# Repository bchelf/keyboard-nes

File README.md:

# keyboard-nes

Remapping order: Right, Left, Down, Up, A, B, Select, Start

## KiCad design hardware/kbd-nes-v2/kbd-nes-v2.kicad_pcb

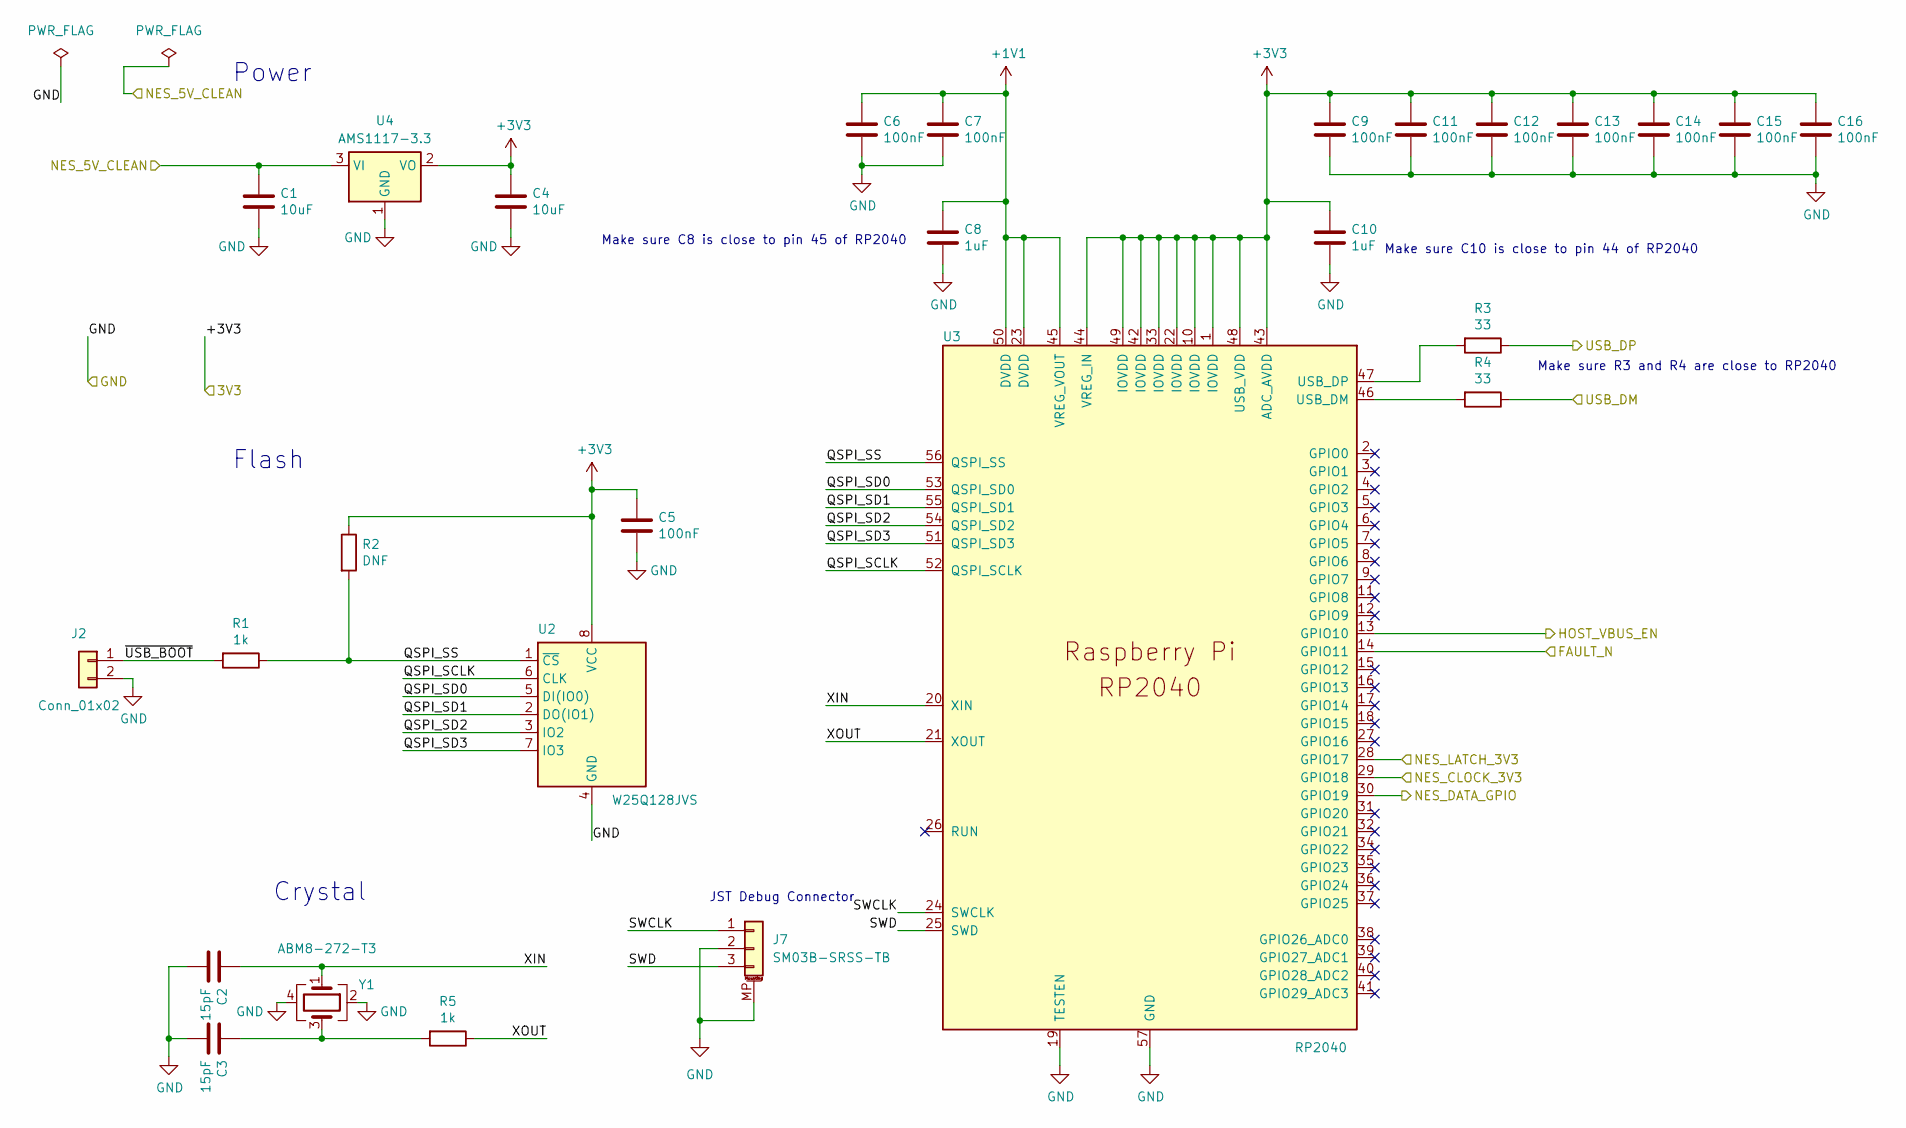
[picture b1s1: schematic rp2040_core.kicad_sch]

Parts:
C1, C4: 10uF; C_0603_1608Metric; LCSC C19702
C2, C3: 15pF; C_0402_1005Metric; LCSC C1548
C5, C6, C7, C9, C11, C12, C13, C14, C15, C16: 100nF; C_0402_1005Metric; LCSC C307331
C8, C10: 1uF; C_0402_1005Metric; LCSC C52923
J2: Conn_01x02; PinHeader_1x02_P2.54mm_Vertical
J7: SM03B-SRSS-TB; JST_SH_SM03B-SRSS-TB_1x03-1MP_P1.00mm_Horizontal; LCSC C160403
R1, R5: 1k; R_0402_1005Metric; LCSC C11702
R2: DNF; R_0402_1005Metric
R3, R4: 33; R_0402_1005Metric; LCSC C25105
U2: W25Q128JVS; SOIC-8_5.3x5.3mm_P1.27mm; LCSC C97521
U3: RP2040; QFN-56-1EP_7x7mm_P0.4mm_EP3.2x3.2mm_ThermalVias; LCSC C2040
U4: AMS1117-3.3; SOT-223-3_TabPin2; LCSC C6186
Y1: ABM8-272-T3; Crystal_SMD_3225-4Pin_3.2x2.5mm; LCSC C20625731

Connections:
+1V1: C6.1, C7.1, C8.1, U3.23 (DVDD), U3.45 (VREG_VOUT), U3.50 (DVDD)
+3V3: C4.1, C5.1, C9.1, C10.1, C11.1, C12.1, C13.1, C14.1, C15.1, C16.1, R2.1, U2.8 (VCC), U3.1 (IOVDD), U3.10 (IOVDD), U3.22 (IOVDD), U3.33 (IOVDD), U3.42 (IOVDD), U3.43 (ADC_AVDD), U3.44 (VREG_IN), U3.48 (USB_VDD), U3.49 (IOVDD), U4.2 (VO); also elsewhere on the board
/NES Input Output/NES_5V_CLEAN: C1.1, U4.3 (VI); also elsewhere on the board
/NES Input Output/NES_CLOCK_3V3: U3.29 (GPIO18); also elsewhere on the board
/NES Input Output/NES_DATA_GPIO: U3.30 (GPIO19); also elsewhere on the board
/NES Input Output/NES_LATCH_3V3: U3.28 (GPIO17); also elsewhere on the board
/RP2040 Core/FAULT_N: U3.14 (GPIO11); also elsewhere on the board
/RP2040 Core/HOST_VBUS_EN: U3.13 (GPIO10); also elsewhere on the board
/RP2040 Core/QSPI_SCLK: U2.6 (CLK), U3.52 (QSPI_SCLK)
/RP2040 Core/QSPI_SD0: U2.5 (DI(IO0)), U3.53 (QSPI_SD0)
/RP2040 Core/QSPI_SD1: U2.2 (DO(IO1)), U3.55 (QSPI_SD1)
/RP2040 Core/QSPI_SD2: U2.3 (IO2), U3.54 (QSPI_SD2)
/RP2040 Core/QSPI_SD3: U2.7 (IO3), U3.51 (QSPI_SD3)
/RP2040 Core/QSPI_SS: R1.1, R2.2, U2.1 (~CS), U3.56 (QSPI_SS)
/RP2040 Core/SWCLK: J7.1, U3.24 (SWCLK)
/RP2040 Core/SWD: J7.3, U3.25 (SWD)
/RP2040 Core/USB_DM: R4.1; also elsewhere on the board
/RP2040 Core/USB_DP: R3.1; also elsewhere on the board
/RP2040 Core/XIN: C2.1, U3.20 (XIN), Y1.1
/RP2040 Core/XOUT: R5.1, U3.21 (XOUT)
/RP2040 Core/~USB_BOOT: J2.1, R1.2
GND: C1.2, C2.2, C3.2, C4.2, C5.2, C6.2, C7.2, C8.2, C9.2, C10.2, C11.2, C12.2, C13.2, C14.2, C15.2, C16.2, J2.2, J7.2, J7.MP (MountPin), U2.4 (GND), U3.19 (TESTEN), U3.57 (GND), U4.1 (GND), Y1.2, Y1.4; also elsewhere on the board
unnamed: C3.1, R5.2, Y1.3
unnamed: R4.2, U3.46 (USB_DM)
unnamed: R3.2, U3.47 (USB_DP)

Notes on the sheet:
Make sure R3 and R4 are close to RP2040
JST Debug Connector
Crystal
Flash
Make sure C8 is close to pin 45 of RP2040
Make sure C10 is close to pin 44 of RP2040
Power

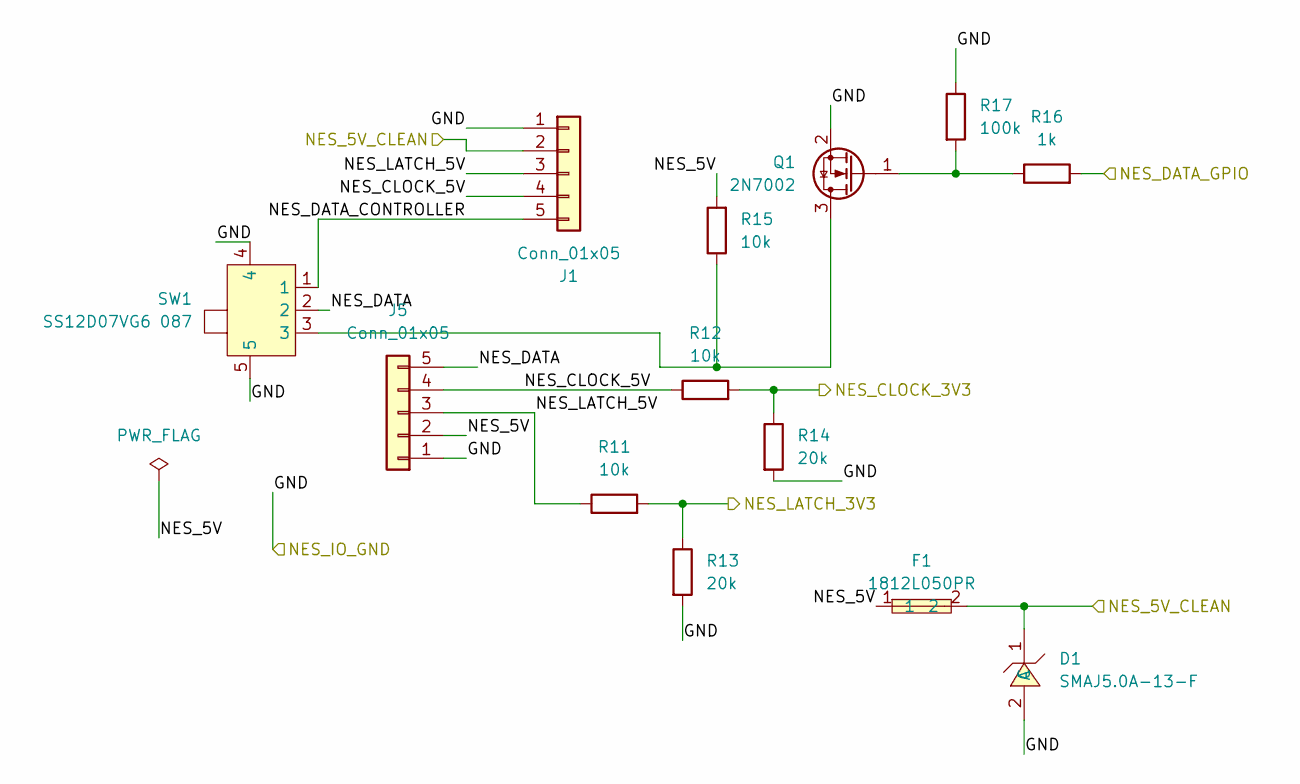
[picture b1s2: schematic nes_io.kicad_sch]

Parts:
D1: SMAJ5.0A-13-F; SMA_L4.3-W2.6-LS5.2-RD; MPN SMAJ5.0A-13-F; LCSC C87074
F1: 1812L050PR; F1812; MPN 1812L050PR; LCSC C151169
J1, J5: Conn_01x05; JST_PH_S5B-PH-SM4-TB_1x05-1MP_P2.00mm_Horizontal; LCSC C265104
Q1: 2N7002; SOT-23; LCSC C8545
R11, R12, R15: 10k; R_0402_1005Metric; LCSC C25744
R13, R14: 20k; R_0402_1005Metric; LCSC C25765
R16: 1k; R_0402_1005Metric; LCSC C11702
R17: 100k; R_0402_1005Metric; LCSC C25741
SW1: SS12D07VG6 087; SW-TH_SS12D07VG4; MPN SS12D07VG6 087; LCSC C2939728

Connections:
/NES Input Output/NES_5V: F1.1, J5.2, R15.2
/NES Input Output/NES_5V_CLEAN: D1.1 (C), F1.2, J1.2; also elsewhere on the board
/NES Input Output/NES_CLOCK_3V3: R12.2, R14.1; also elsewhere on the board
/NES Input Output/NES_CLOCK_5V: J1.4, J5.4, R12.1
/NES Input Output/NES_DATA: J5.5, SW1.2
/NES Input Output/NES_DATA_CONTROLLER: J1.5, SW1.1
/NES Input Output/NES_DATA_GPIO: R16.2; also elsewhere on the board
/NES Input Output/NES_LATCH_3V3: R11.2, R13.1; also elsewhere on the board
/NES Input Output/NES_LATCH_5V: J1.3, J5.3, R11.1
GND: D1.2 (A), J1.1, J5.1, Q1.2 (S), R13.2, R14.2, R17.1, SW1.4, SW1.5; also elsewhere on the board
unnamed: Q1.3 (D), R15.1, SW1.3
unnamed: Q1.1 (G), R16.1, R17.2

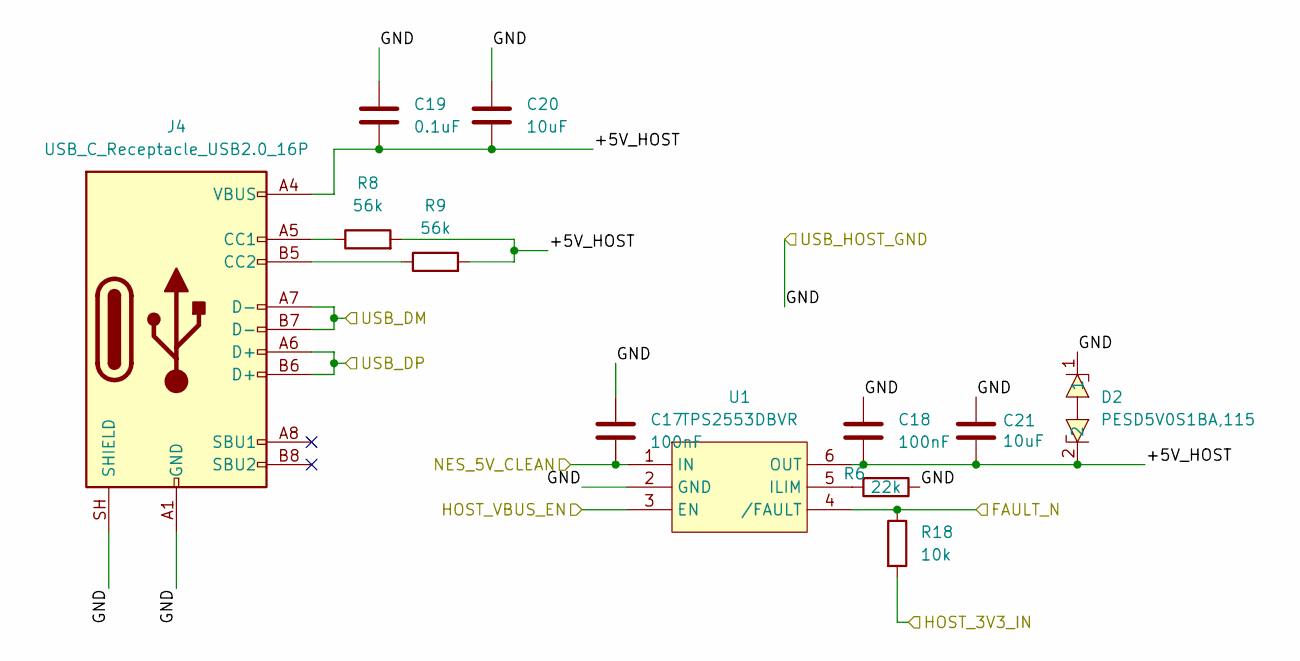
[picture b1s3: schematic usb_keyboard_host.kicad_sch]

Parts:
C17, C18: 100nF; C_0402_1005Metric; LCSC C307331
C19: 0.1uF; C_0402_1005Metric; LCSC C307331
C20: 10uF; C_0603_1608Metric
C21: 10uF; C_0603_1608Metric; LCSC C19702
D2: PESD5V0S1BA,115; SOD-323_L1.7-W1.3-LS2.5-BI; MPN PESD5V0S1BA,115; LCSC C19224
J4: USB_C_Receptacle_USB2.0_16P; USB_C_Receptacle_HRO_TYPE-C-31-M-12; LCSC C165948
R6: 22k; R_0402_1005Metric; LCSC C25768
R8, R9: 56k; R_0603_1608Metric; LCSC C23206
R18: 10k; R_0402_1005Metric; LCSC C25744
U1: TPS2553DBVR; SOT-23-6_L2.9-W1.6-P0.95-LS2.8-BR; MPN TPS2553DBVR; LCSC C55266

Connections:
+3V3: R18.2; also elsewhere on the board
/NES Input Output/NES_5V_CLEAN: C17.2, U1.1 (IN); also elsewhere on the board
/RP2040 Core/FAULT_N: R18.1, U1.4 (/FAULT); also elsewhere on the board
/RP2040 Core/HOST_VBUS_EN: U1.3 (EN); also elsewhere on the board
/RP2040 Core/USB_DM: J4.A7 (D-), J4.B7 (D-); also elsewhere on the board
/RP2040 Core/USB_DP: J4.A6 (D+), J4.B6 (D+); also elsewhere on the board
/USB Keyboard Host/+5V_HOST: C18.2, C19.1, C20.1, C21.2, D2.2, J4.A4 (VBUS), J4.A9 (VBUS), J4.B4 (VBUS), J4.B9 (VBUS), R8.2, R9.2, U1.6 (OUT)
GND: C17.1, C18.1, C19.2, C20.2, C21.1, D2.1, J4.A1 (GND), J4.A12 (GND), J4.B1 (GND), J4.B12 (GND), J4.SH (SHIELD), R6.1, U1.2 (GND); also elsewhere on the board
unnamed: J4.A5 (CC1), R8.1
unnamed: J4.B5 (CC2), R9.1
unnamed: R6.2, U1.5 (ILIM)

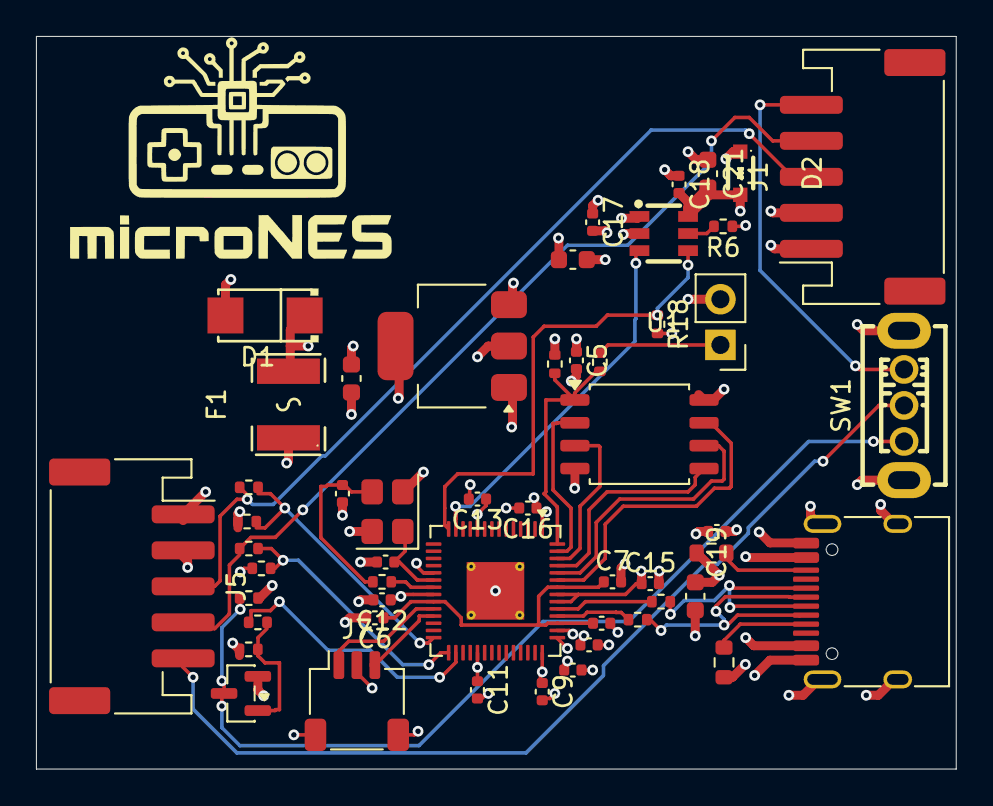
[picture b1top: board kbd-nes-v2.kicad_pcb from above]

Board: 4 copper layers, 51.1 x 40.7 mm, 52 parts (0 on the bottom side), 36 nets.

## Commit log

2026-04-07 intial implementation
2026-04-07 get initial thing working hurray
2026-04-07 codex fixes to make button presses more reliable - only latency left
2026-04-07 First attempt at latency fixes
2026-04-07 remove printfs to reduce lag haha
2026-04-15 hardware implementation phase 1
2026-04-16 final submitted CAD to JLC
2026-04-28 fix polarity of NES data pin
2026-04-28 turn off logging by default and change FIFO behavior to be smarter
2026-05-14 add v2 board with switch
2026-05-14 Add key bindings reset - need to test - and also fix schematic and PCB for diode
